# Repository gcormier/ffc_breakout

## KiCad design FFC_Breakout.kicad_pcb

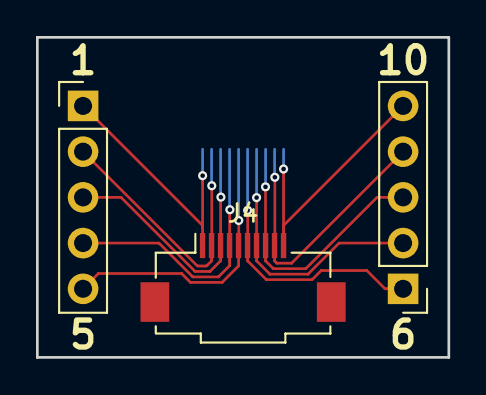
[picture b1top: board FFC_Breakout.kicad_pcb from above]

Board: 2 copper layers, 22.9 x 17.8 mm, 4 parts (1 on the bottom side), 10 nets.

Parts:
J1: LEFT; PinHeader_1x05_P2.54mm_Vertical
J2: RIGHT; PinHeader_1x05_P2.54mm_Vertical
J3, J4: FFC_10; Molex_52892-1033_1x10-1MP_P0.5mm_Horizontal

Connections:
unnamed: J1.1, J3.1, J4.1
unnamed: J1.2, J3.2, J4.2
unnamed: J1.3, J3.3, J4.3
unnamed: J1.4, J3.4, J4.4
unnamed: J1.5, J3.5, J4.5
unnamed: J2.1, J3.6, J4.6
unnamed: J2.2, J3.7, J4.7
unnamed: J2.3, J3.8, J4.8
unnamed: J2.4, J3.9, J4.9
unnamed: J2.5, J3.10, J4.10

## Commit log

2018-10-12 intercept
